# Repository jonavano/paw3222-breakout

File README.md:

# PAW3222 PCB

[PixArt PAW3222LU-TJDU](https://www.pixart.com/products-detail/16/PAW3222LU-TJDU) low power laser mouse sensor breakout board.

- Be operated with 3.3V voltage level ONLY.
- Outlined as narrow as possible for side mount horizontally and perpendicular on low profile keyboards.

*Figure 1: Size comparing to Seeed XIAO BLE*

## PCB

Online preview avaliable [here](https://kicanvas.org/?github=https%3A%2F%2Fgithub.com%2Fbadjeff%2Fpaw3222-pcb), powered by [KiCanvas](https://github.com/theacodes/kicanvas).

*Figure 2: PCB edgecuts dimension*

*Figure 3: PCB 3D View - 1.6mm FR4*

### BOM

|Designator|Footprint|Quantity|Value|LCSC Part #|
|-|-|-|-|-|
|C1|SMD 0402|1|100nF||
|C2|SMD 0402|1|10uF||
|C3|SMD 0402|1|4.7uF||
|R1|SMD 0402|1|51R||
|U1|PAW3222LU-TJDU|1|PAW3222LU-TJDU||
|D1|LTE-C216-P-W|1|LTE-C216-P-W||
|J1|1.27mm Pin header|1|1x6||

- SMD 0402 (Imperial) aka 1005 Metric.
- PAW3222LU-TJDU needs to be used with PNSR-015-RB3 lens.

### Board Characteristics

- Copper layer count: 2
- Board thickness: 1.6 mm or 1.2mm
- Board overall dimensions: 7.75 x 12.53 mm

### Voltage level config

- 3.3V logic
- VIN: 3.3V

## License

Available under the [CERN-OHL-P v2](/LICENSE) permissive license.

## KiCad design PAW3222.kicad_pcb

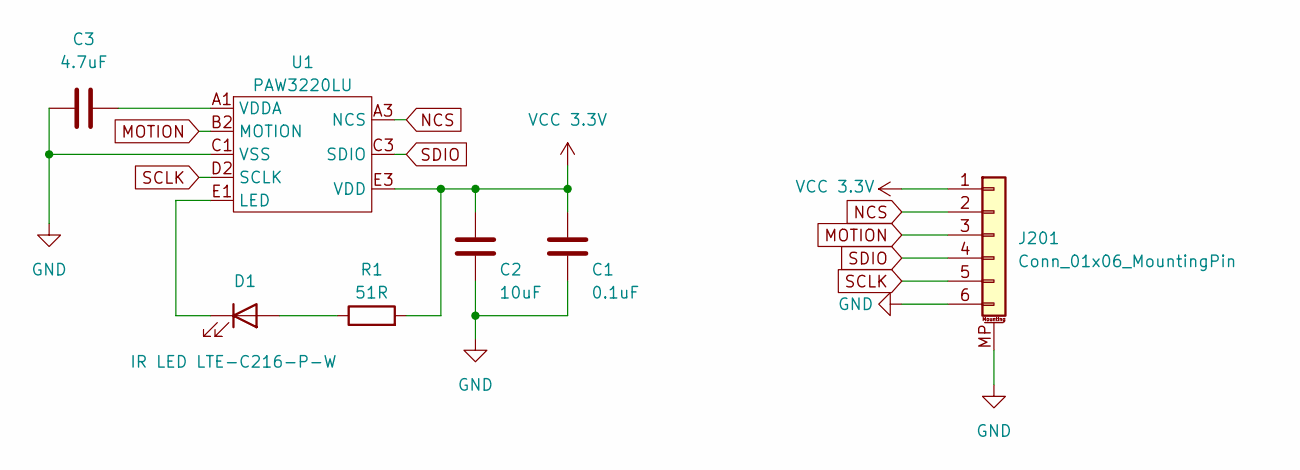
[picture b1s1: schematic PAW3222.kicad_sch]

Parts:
C1: 0.1uF; C_0402_1005Metric
C2: 10uF; C_0402_1005Metric
C3: 4.7uF; C_0402_1005Metric
D1: IR LED LTE-C216-P-W; LTE-C216-P-W; LCSC C2942980
J201: Conn_01x06_MountingPin; GT-F0501SR10-06S1101
R1: 51R; R_0402_1005Metric
U1: PAW3220LU; PAW3222LU; LCSC C9900022540

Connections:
GND: C1.2, C2.2, C3.2, J201.6, J201.MP (MountPin), U1.C1 (VSS)
MOTION: J201.3, U1.B2 (MOTION)
NCS: J201.2, U1.A3 (NCS)
unnamed: D1.2 (A), R1.1
unnamed: D1.1 (K), U1.E1 (LED)
unnamed: C3.1, U1.A1 (VDDA)
SCLK: J201.5, U1.D2 (SCLK)
SDIO: J201.4, U1.C3 (SDIO)
VCC 3.3V: C1.1, C2.1, J201.1, R1.2, U1.E3 (VDD)

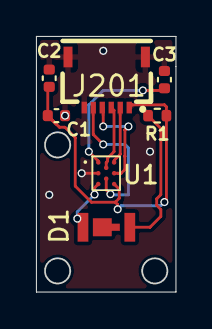
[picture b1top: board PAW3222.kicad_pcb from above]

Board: 2 copper layers, 7.7 x 14.2 mm, 7 parts (0 on the bottom side), 9 nets.

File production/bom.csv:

Designator,Footprint,Quantity,Value,LCSC Part #
C1,0402,1,0.1uF,
C2,0402,1,10uF,
C3,0402,1,4.7uF,
D1,LTE-C216-P-W,1,IR LED LTE-C216-P-W,C2942980
J201,GT-F0501SR10-06S1101,1,Conn_01x06_MountingPin,
R1,0402,1,51R,
U1,PAW3222LU,1,PAW3220LU,C9900022540

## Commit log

2025-11-01 add README.md
2025-11-09 add photo-1
2025-12-09 update pcb to ffc cable connector
2025-12-11 flip pin out
2025-12-11 fix other
